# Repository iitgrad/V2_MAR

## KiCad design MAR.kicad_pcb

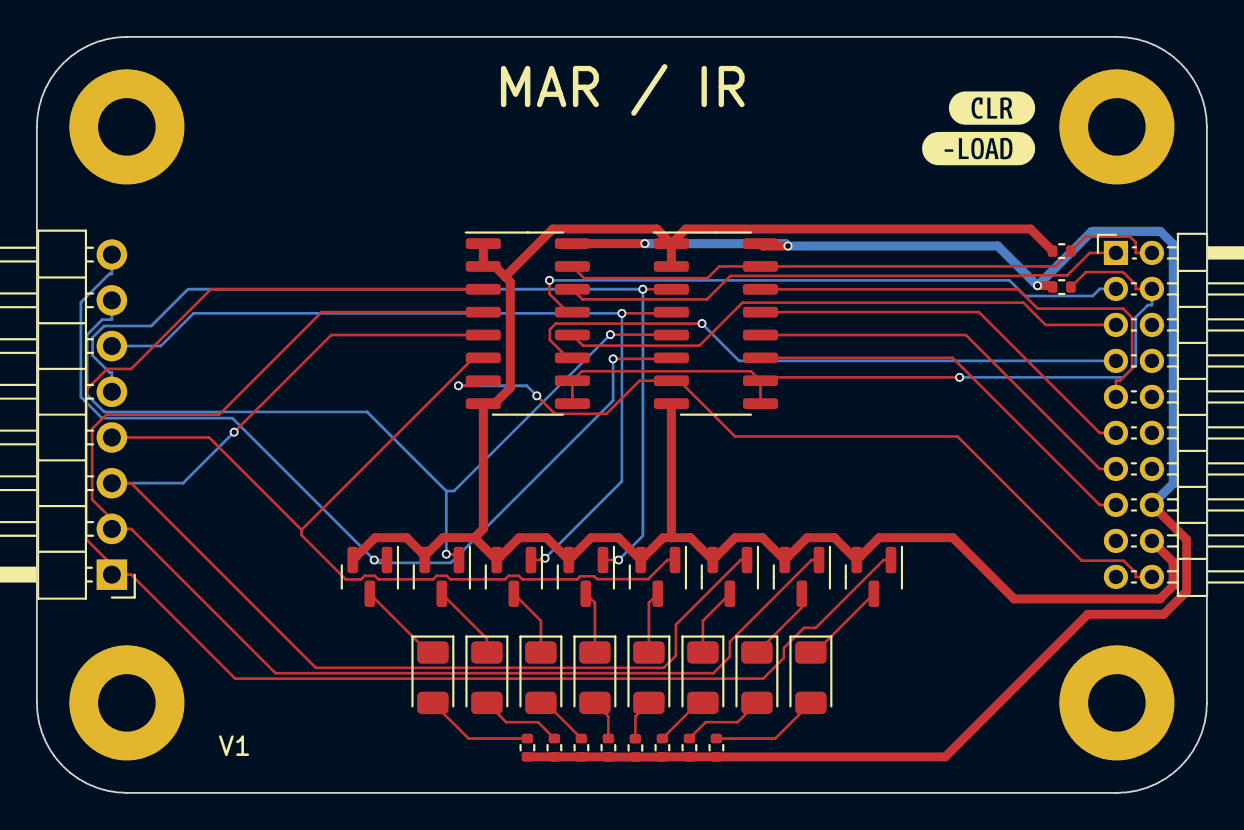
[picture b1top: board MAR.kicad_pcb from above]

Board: 2 copper layers, 65.0 x 42.0 mm, 36 parts (0 on the bottom side), 37 nets.

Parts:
D1, D2, D3, D4, D5, D6, D7, D8: RED; LED_1206_3216Metric
H1, H2, H3, H4: MountingHole_3.2mm_M3_Pad
J1: Conn_02x10_Odd_Even; PinHeader_2x10_P2.00mm_Horizontal
J2: Conn_01x08_Pin; PinHeader_1x08_P2.54mm_Horizontal
Q1, Q2, Q3, Q4, Q5, Q6, Q7, Q8: DMN3404; SOT-23
R1, R2, R3, R4, R5, R6, R7, R8: 330; R_0402_1005Metric
R9, R10: 10K; R_0402_1005Metric
U1, U2: 74HC173; SOIC-16_3.9x9.9mm_P1.27mm
kibuzzard-6571E777: G***; kibuzzard-6571E777
kibuzzard-6571E781: G***; kibuzzard-6571E781

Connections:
/D0: J1.1, U1.14 (D0)
/D1: J1.3, U1.13 (D1)
/D2: J1.5, U1.12 (D2)
/D3: J1.7, U1.11 (D3)
/D4: J1.9, U2.14 (D0)
/D5: J1.11, U2.13 (D1)
/D6: J1.13, U2.12 (D2)
/D7: J1.15, U2.11 (D3)
/Q0: J2.1, Q1.1 (G), U1.3 (Q0)
/Q1: J2.2, Q2.1 (G), U1.4 (Q1)
/Q2: J2.3, Q3.1 (G), U1.5 (Q2)
/Q3: J2.4, Q4.1 (G), U1.6 (Q3)
/Q4: J2.5, Q5.1 (G), U2.3 (Q0)
/Q5: J2.6, Q6.1 (G), U2.4 (Q1)
/Q6: J2.7, Q7.1 (G), U2.5 (Q2)
/Q7: J2.8, Q8.1 (G), U2.6 (Q3)
CLK: J1.20, U1.7 (Cp), U2.7 (Cp)
CLR: J1.2, R10.2, U1.15 (Mr), U2.15 (Mr)
GND: J1.18, Q1.2 (S), Q2.2 (S), Q3.2 (S), Q4.2 (S), Q5.2 (S), Q6.2 (S), Q7.2 (S), Q8.2 (S), R10.1, U1.1 (Oe1), U1.2 (Oe2), U1.8 (GND), U2.1 (Oe1), U2.2 (Oe2), U2.8 (GND)
unnamed: D1.2 (A), R1.1
unnamed: D1.1 (K), Q1.3 (D)
unnamed: D2.2 (A), R2.1
unnamed: D2.1 (K), Q2.3 (D)
unnamed: D3.2 (A), R3.1
unnamed: D3.1 (K), Q3.3 (D)
unnamed: D4.2 (A), R4.1
unnamed: D4.1 (K), Q4.3 (D)
unnamed: D5.2 (A), R5.1
unnamed: D5.1 (K), Q5.3 (D)
unnamed: D6.2 (A), R6.1
unnamed: D6.1 (K), Q6.3 (D)
unnamed: D7.2 (A), R7.1
unnamed: D7.1 (K), Q7.3 (D)
unnamed: D8.2 (A), R8.1
unnamed: D8.1 (K), Q8.3 (D)
VCC: J1.16, R1.2, R2.2, R3.2, R4.2, R5.2, R6.2, R7.2, R8.2, R9.2, U1.16 (VCC), U2.16 (VCC)
~LOAD: J1.4, R9.1, U1.9 (E1), U1.10 (E2), U2.9 (E1), U2.10 (E2)

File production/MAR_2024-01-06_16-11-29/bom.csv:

Designator,Footprint,Quantity,Value,LCSC Part #
"D1, D2, D3, D4, D5, D6, D7, D8",1206,8,RED,C434438
J1,PinHeader_2x10_P2.00mm_Horizontal,1,Conn_02x10_Odd_Even,C376110
J2,PinHeader_1x08_P2.54mm_Horizontal,1,Conn_01x08_Pin,C2894950
"Q1, Q2, Q3, Q4, Q5, Q6, Q7, Q8",SOT-23,8,DMN3404,C155257
"R1, R2, R3, R4, R5, R6, R7, R8",0402,8,330,C25104
"R10, R9",0402,2,10K,C60490
"U1, U2",SOIC-16_3.9x9.9mm_P1.27mm,2,74HC173,C546651

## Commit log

2024-01-06 increased resistor values for leds
2024-02-28 fixed grid alignment issue in schematic
